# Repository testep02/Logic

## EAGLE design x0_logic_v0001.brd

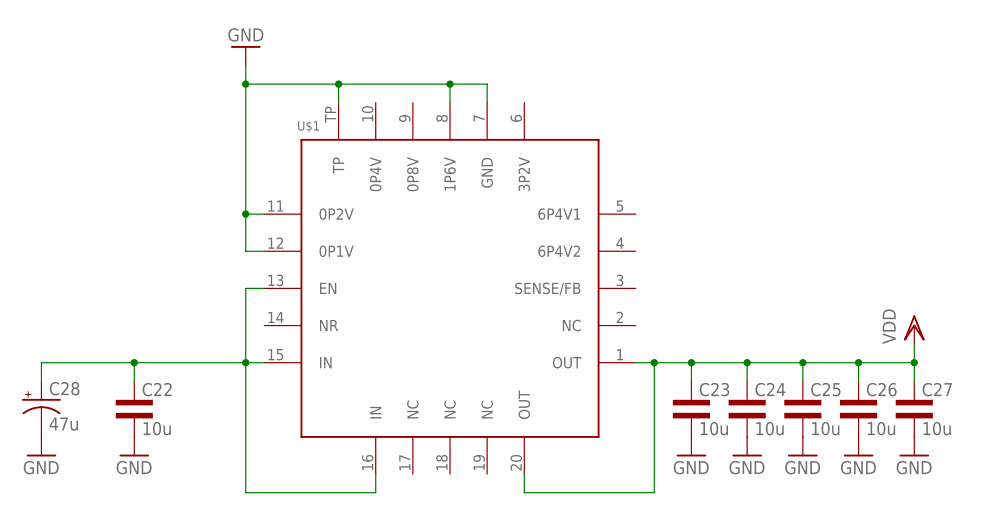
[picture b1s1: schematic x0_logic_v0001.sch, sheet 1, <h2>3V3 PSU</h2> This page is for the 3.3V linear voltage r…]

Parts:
C22, C23, C24, C25, C26, C27: 10u; 1206L3
C28: 47u; CT7343
U$1: POWER-SUPPLY_POS_V1_TI_LDO_TPS7A4700; POWER-SUPPLY_POS_V1_TI_LDO_VQFN-20

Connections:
BATT+: C22.1, C28.+, U$1.13 (EN), U$1.15 (IN), U$1.16 (IN); also elsewhere on the board
GND: C22.2, C23.2, C24.2, C25.2, C26.2, C27.2, C28.-, U$1.7 (GND), U$1.8 (1P6V), U$1.11 (0P2V), U$1.12 (0P1V), U$1.TP; also elsewhere on the board
VDD: C23.1, C24.1, C25.1, C26.1, C27.1, U$1.1 (OUT), U$1.20 (OUT); also elsewhere on the board

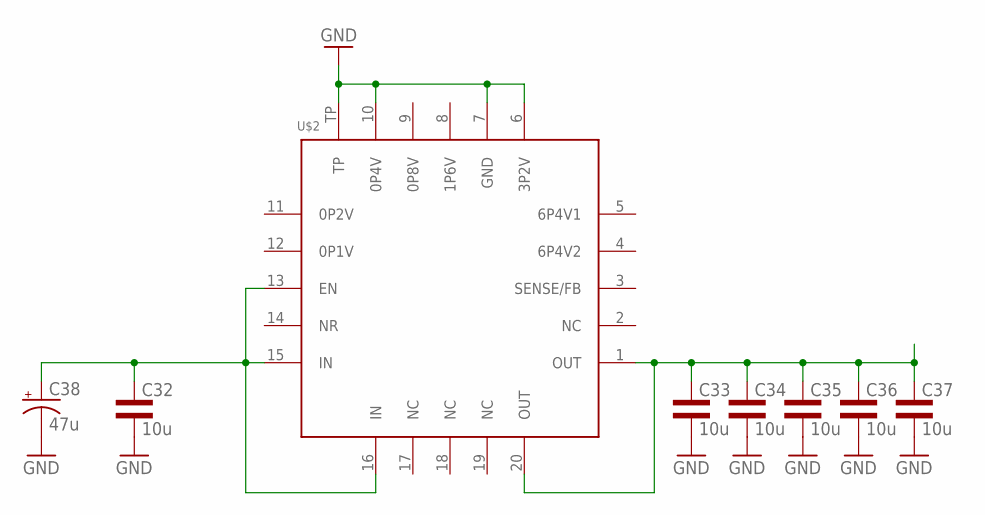
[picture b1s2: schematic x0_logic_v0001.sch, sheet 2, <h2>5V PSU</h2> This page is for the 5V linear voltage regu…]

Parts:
C32, C33, C34, C35, C36, C37: 10u; 1206L3
C38: 47u; CT7343
U$2: POWER-SUPPLY_POS_V1_TI_LDO_TPS7A4700; POWER-SUPPLY_POS_V1_TI_LDO_VQFN-20

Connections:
5V: C33.1, C34.1, C35.1, C36.1, C37.1, U$2.1 (OUT), U$2.20 (OUT); also elsewhere on the board
BATT+: C32.1, C38.+, U$2.13 (EN), U$2.15 (IN), U$2.16 (IN); also elsewhere on the board
GND: C32.2, C33.2, C34.2, C35.2, C36.2, C37.2, C38.-, U$2.6 (3P2V), U$2.7 (GND), U$2.10 (0P4V), U$2.TP; also elsewhere on the board

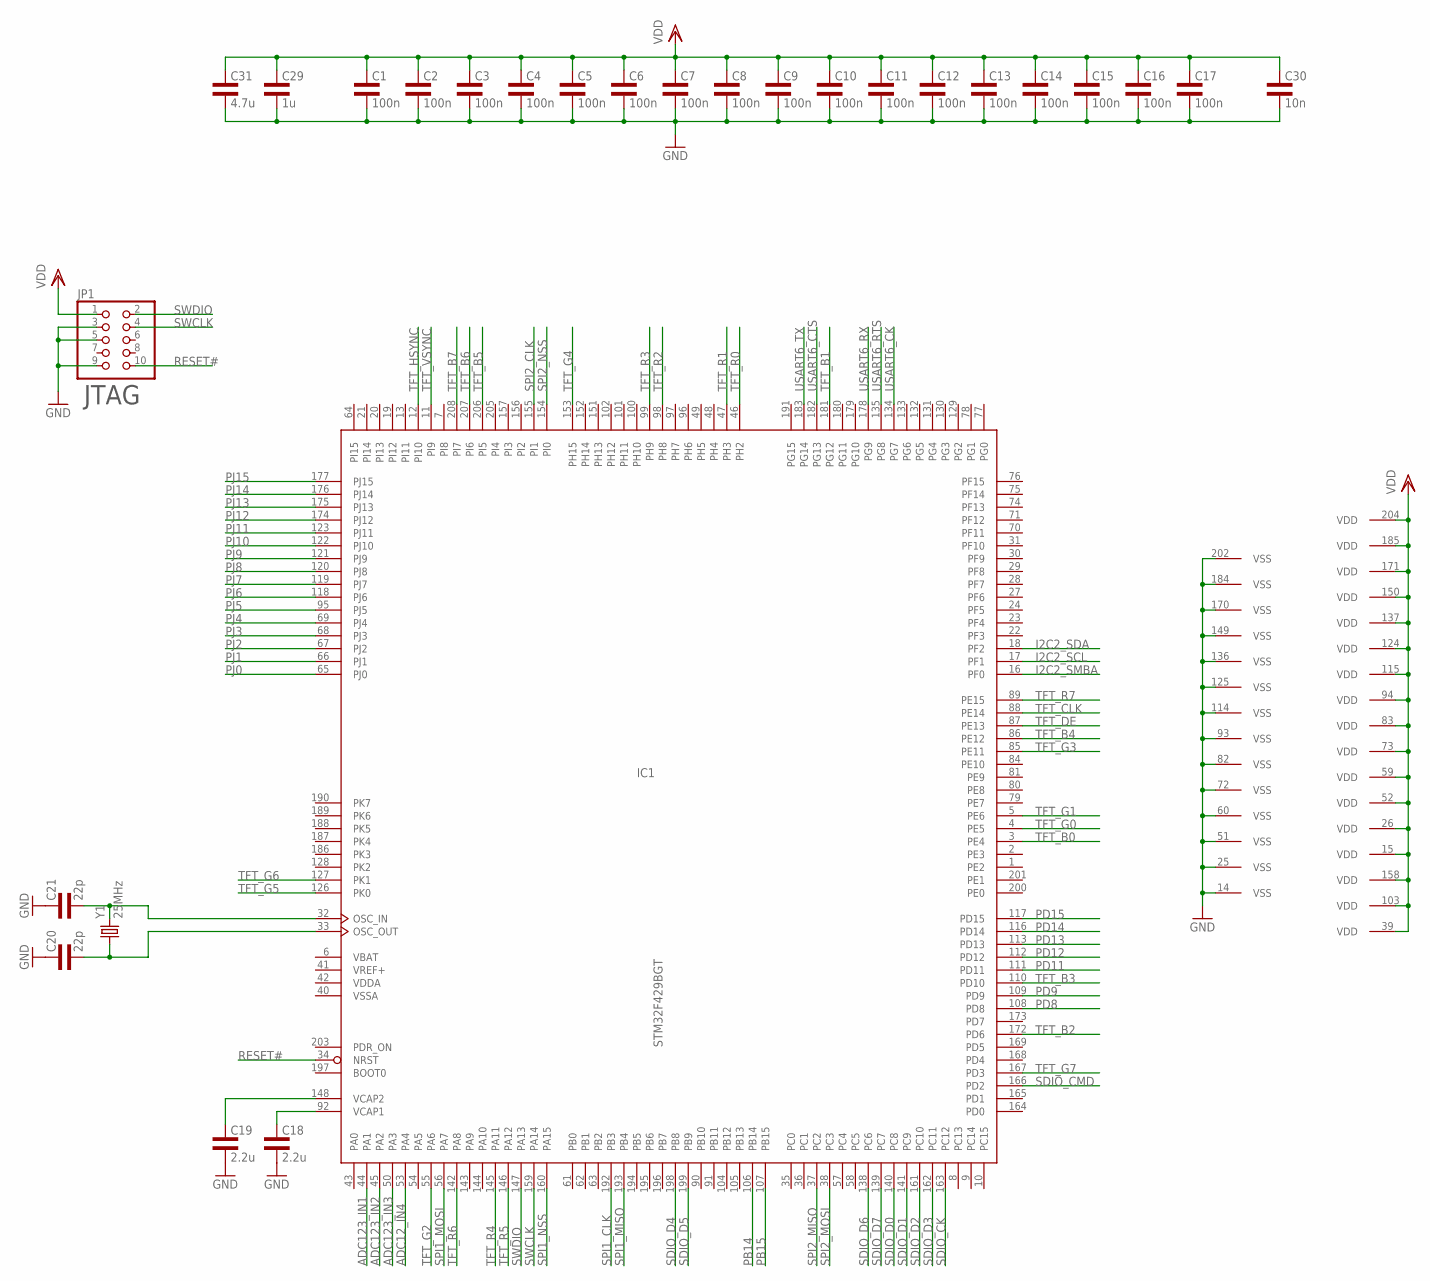
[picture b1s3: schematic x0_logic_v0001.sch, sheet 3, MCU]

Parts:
C1, C2, C3, C4, C5, C6, C7, C8, C9, C10, C11, C12, C13, C14, C15, C16, C17: 100n; 0402L3
C18, C19: 2.2u; 0603L3
C20, C21: 22p; 0402L3
C29: 1u; 0805L3
C30: 10n; 0603L3
C31: 4.7u; 0805L3
IC1: STM32F429BGT; LQFP208
JP1: PINHD-2X5; 2X05
Y1: 25MHz; HC49US

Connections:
ADC12_IN4: IC1.53 (PA4); also elsewhere on the board
ADC123_IN1: IC1.44 (PA1); also elsewhere on the board
ADC123_IN2: IC1.45 (PA2); also elsewhere on the board
ADC123_IN3: IC1.50 (PA3); also elsewhere on the board
GND: C1.P$2 (2), C2.P$2 (2), C3.P$2 (2), C4.P$2 (2), C5.P$2 (2), C6.P$2 (2), C7.P$2 (2), C8.P$2 (2), C9.P$2 (2), C10.P$2 (2), C11.P$2 (2), C12.P$2 (2), C13.P$2 (2), C14.P$2 (2), C15.P$2 (2), C16.P$2 (2), C17.P$2 (2), C18.P$2 (2), C19.P$2 (2), C20.P$1 (1), C21.P$1 (1), C29.2, C30.P$2 (2), C31.2, IC1.14 (VSS), IC1.25 (VSS), IC1.51 (VSS), IC1.60 (VSS), IC1.72 (VSS), IC1.82 (VSS), IC1.93 (VSS), IC1.114 (VSS), IC1.125 (VSS), IC1.136 (VSS), IC1.149 (VSS), IC1.170 (VSS), IC1.184 (VSS), IC1.202 (VSS), JP1.3, JP1.5, JP1.9; also elsewhere on the board
I2C2_SCL: IC1.17 (PF1); also elsewhere on the board
I2C2_SDA: IC1.18 (PF2); also elsewhere on the board
I2C2_SMBA: IC1.16 (PF0); also elsewhere on the board
unnamed: C18.P$1 (1), IC1.92 (VCAP1)
unnamed: C19.P$1 (1), IC1.148 (VCAP2)
unnamed: C20.P$2 (2), IC1.33 (OSC_OUT), Y1.1
unnamed: C21.P$2 (2), IC1.32 (OSC_IN), Y1.2
PB14: IC1.106 (PB14)
PB15: IC1.107 (PB15); also elsewhere on the board
PD8: IC1.108 (PD8)
PD9: IC1.109 (PD9)
PD11: IC1.111 (PD11)
PD12: IC1.112 (PD12)
PD13: IC1.113 (PD13)
PD14: IC1.116 (PD14)
PD15: IC1.117 (PD15)
PJ0: IC1.65 (PJ0); also elsewhere on the board
PJ1: IC1.66 (PJ1); also elsewhere on the board
PJ2: IC1.67 (PJ2); also elsewhere on the board
PJ3: IC1.68 (PJ3); also elsewhere on the board
PJ4: IC1.69 (PJ4); also elsewhere on the board
PJ5: IC1.95 (PJ5); also elsewhere on the board
PJ6: IC1.118 (PJ6); also elsewhere on the board
PJ7: IC1.119 (PJ7); also elsewhere on the board
PJ8: IC1.120 (PJ8); also elsewhere on the board
PJ9: IC1.121 (PJ9); also elsewhere on the board
PJ10: IC1.122 (PJ10); also elsewhere on the board
PJ11: IC1.123 (PJ11); also elsewhere on the board
PJ12: IC1.174 (PJ12); also elsewhere on the board
PJ13: IC1.175 (PJ13); also elsewhere on the board
PJ14: IC1.176 (PJ14); also elsewhere on the board
PJ15: IC1.177 (PJ15); also elsewhere on the board
RESET#: IC1.34 (NRST), JP1.10
SDIO_CK: IC1.163 (PC12); also elsewhere on the board
SDIO_CMD: IC1.166 (PD2); also elsewhere on the board
SDIO_D0: IC1.140 (PC8); also elsewhere on the board
SDIO_D1: IC1.141 (PC9); also elsewhere on the board
SDIO_D2: IC1.161 (PC10); also elsewhere on the board
SDIO_D3: IC1.162 (PC11); also elsewhere on the board
SDIO_D4: IC1.198 (PB8)
SDIO_D5: IC1.199 (PB9)
SDIO_D6: IC1.138 (PC6)
SDIO_D7: IC1.139 (PC7)
SPI1_CLK: IC1.192 (PB3); also elsewhere on the board
SPI1_MISO: IC1.193 (PB4); also elsewhere on the board
SPI1_MOSI: IC1.56 (PA7); also elsewhere on the board
SPI1_NSS: IC1.160 (PA15); also elsewhere on the board
SPI2_CLK: IC1.155 (PI1); also elsewhere on the board
SPI2_MISO: IC1.37 (PC2); also elsewhere on the board
SPI2_MOSI: IC1.38 (PC3); also elsewhere on the board
SPI2_NSS: IC1.154 (PI0); also elsewhere on the board
SWCLK: IC1.159 (PA14), JP1.4
SWDIO: IC1.147 (PA13), JP1.2
TFT_B0: IC1.3 (PE4); also elsewhere on the board
TFT_B1: IC1.181 (PG12); also elsewhere on the board
TFT_B2: IC1.172 (PD6); also elsewhere on the board
TFT_B3: IC1.110 (PD10); also elsewhere on the board
TFT_B4: IC1.86 (PE12); also elsewhere on the board
TFT_B5: IC1.206 (PI5); also elsewhere on the board
TFT_B6: IC1.207 (PI6); also elsewhere on the board
TFT_B7: IC1.208 (PI7); also elsewhere on the board
TFT_CLK: IC1.88 (PE14); also elsewhere on the board
TFT_DE: IC1.87 (PE13); also elsewhere on the board
TFT_G0: IC1.4 (PE5); also elsewhere on the board
TFT_G1: IC1.5 (PE6); also elsewhere on the board
TFT_G2: IC1.55 (PA6); also elsewhere on the board
TFT_G3: IC1.85 (PE11); also elsewhere on the board
TFT_G4: IC1.153 (PH15); also elsewhere on the board
TFT_G5: IC1.126 (PK0); also elsewhere on the board
TFT_G6: IC1.127 (PK1); also elsewhere on the board
TFT_G7: IC1.167 (PD3); also elsewhere on the board
TFT_HSYNC: IC1.12 (PI10); also elsewhere on the board
TFT_R0: IC1.46 (PH2); also elsewhere on the board
TFT_R1: IC1.47 (PH3); also elsewhere on the board
TFT_R2: IC1.98 (PH8); also elsewhere on the board
TFT_R3: IC1.99 (PH9); also elsewhere on the board
TFT_R4: IC1.145 (PA11); also elsewhere on the board
TFT_R5: IC1.146 (PA12); also elsewhere on the board
TFT_R6: IC1.142 (PA8); also elsewhere on the board
TFT_R7: IC1.89 (PE15); also elsewhere on the board
TFT_VSYNC: IC1.11 (PI9); also elsewhere on the board
USART6_CK: IC1.134 (PG7)
USART6_CTS: IC1.182 (PG13)
USART6_RTS: IC1.135 (PG8)
USART6_RX: IC1.178 (PG9)
USART6_TX: IC1.183 (PG14)
VBAT: IC1.6 (VBAT)
VDD: C1.P$1 (1), C2.P$1 (1), C3.P$1 (1), C4.P$1 (1), C5.P$1 (1), C6.P$1 (1), C7.P$1 (1), C8.P$1 (1), C9.P$1 (1), C10.P$1 (1), C11.P$1 (1), C12.P$1 (1), C13.P$1 (1), C14.P$1 (1), C15.P$1 (1), C16.P$1 (1), C17.P$1 (1), C29.1, C30.P$1 (1), C31.1, IC1.15 (VDD), IC1.26 (VDD), IC1.39 (VDD), IC1.52 (VDD), IC1.59 (VDD), IC1.73 (VDD), IC1.83 (VDD), IC1.94 (VDD), IC1.103 (VDD), IC1.115 (VDD), IC1.124 (VDD), IC1.137 (VDD), IC1.150 (VDD), IC1.158 (VDD), IC1.171 (VDD), IC1.185 (VDD), IC1.204 (VDD), JP1.1; also elsewhere on the board
VDDA: IC1.42 (VDDA)
VREF+: IC1.41 (VREF+)
VSSA: IC1.40 (VSSA)

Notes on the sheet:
JTAG

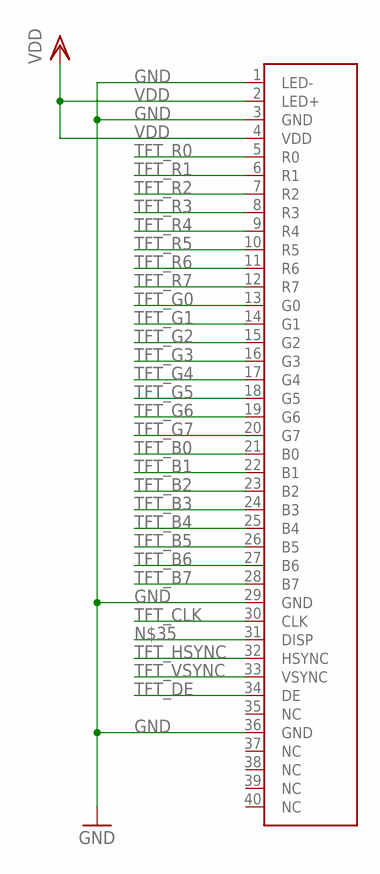
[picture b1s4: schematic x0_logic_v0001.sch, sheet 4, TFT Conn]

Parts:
CON1: NH-4.3; FPC-40

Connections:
GND: CON1.1 (LED-), CON1.3 (GND), CON1.29 (GND), CON1.36 (GND); also elsewhere on the board
TFT_B0: CON1.21 (B0); also elsewhere on the board
TFT_B1: CON1.22 (B1); also elsewhere on the board
TFT_B2: CON1.23 (B2); also elsewhere on the board
TFT_B3: CON1.24 (B3); also elsewhere on the board
TFT_B4: CON1.25 (B4); also elsewhere on the board
TFT_B5: CON1.26 (B5); also elsewhere on the board
TFT_B6: CON1.27 (B6); also elsewhere on the board
TFT_B7: CON1.28 (B7); also elsewhere on the board
TFT_CLK: CON1.30 (CLK); also elsewhere on the board
TFT_DE: CON1.34 (DE); also elsewhere on the board
TFT_G0: CON1.13 (G0); also elsewhere on the board
TFT_G1: CON1.14 (G1); also elsewhere on the board
TFT_G2: CON1.15 (G2); also elsewhere on the board
TFT_G3: CON1.16 (G3); also elsewhere on the board
TFT_G4: CON1.17 (G4); also elsewhere on the board
TFT_G5: CON1.18 (G5); also elsewhere on the board
TFT_G6: CON1.19 (G6); also elsewhere on the board
TFT_G7: CON1.20 (G7); also elsewhere on the board
TFT_HSYNC: CON1.32 (HSYNC); also elsewhere on the board
TFT_R0: CON1.5 (R0); also elsewhere on the board
TFT_R1: CON1.6 (R1); also elsewhere on the board
TFT_R2: CON1.7 (R2); also elsewhere on the board
TFT_R3: CON1.8 (R3); also elsewhere on the board
TFT_R4: CON1.9 (R4); also elsewhere on the board
TFT_R5: CON1.10 (R5); also elsewhere on the board
TFT_R6: CON1.11 (R6); also elsewhere on the board
TFT_R7: CON1.12 (R7); also elsewhere on the board
TFT_VSYNC: CON1.33 (VSYNC); also elsewhere on the board
VDD: CON1.2 (LED+), CON1.4 (VDD); also elsewhere on the board

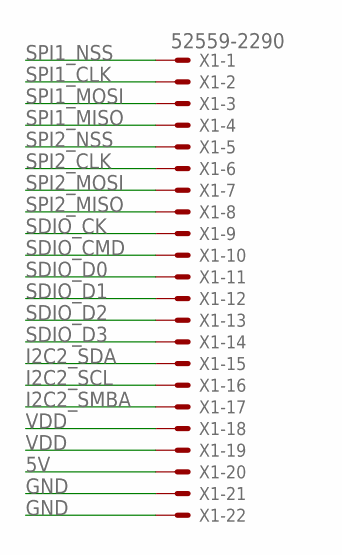
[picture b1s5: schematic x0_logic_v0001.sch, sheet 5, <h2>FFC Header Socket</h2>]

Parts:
X1: 52559-2290

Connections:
5V: X1.20; also elsewhere on the board
GND: X1.21, X1.22; also elsewhere on the board
I2C2_SCL: X1.16; also elsewhere on the board
I2C2_SDA: X1.15; also elsewhere on the board
I2C2_SMBA: X1.17; also elsewhere on the board
SDIO_CK: X1.9; also elsewhere on the board
SDIO_CMD: X1.10; also elsewhere on the board
SDIO_D0: X1.11; also elsewhere on the board
SDIO_D1: X1.12; also elsewhere on the board
SDIO_D2: X1.13; also elsewhere on the board
SDIO_D3: X1.14; also elsewhere on the board
SPI1_CLK: X1.2; also elsewhere on the board
SPI1_MISO: X1.4; also elsewhere on the board
SPI1_MOSI: X1.3; also elsewhere on the board
SPI1_NSS: X1.1; also elsewhere on the board
SPI2_CLK: X1.6; also elsewhere on the board
SPI2_MISO: X1.8; also elsewhere on the board
SPI2_MOSI: X1.7; also elsewhere on the board
SPI2_NSS: X1.5; also elsewhere on the board
VDD: X1.18, X1.19; also elsewhere on the board

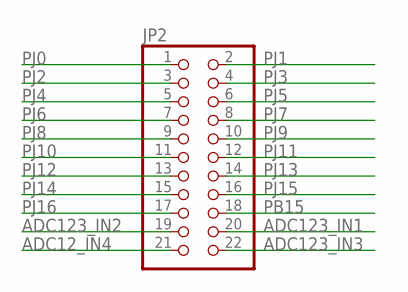
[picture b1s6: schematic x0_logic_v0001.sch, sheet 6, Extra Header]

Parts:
JP2: PINHD-2X11; 2X11

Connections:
ADC12_IN4: JP2.21; also elsewhere on the board
ADC123_IN1: JP2.20; also elsewhere on the board
ADC123_IN2: JP2.19; also elsewhere on the board
ADC123_IN3: JP2.22; also elsewhere on the board
PB15: JP2.18; also elsewhere on the board
PJ0: JP2.1; also elsewhere on the board
PJ1: JP2.2; also elsewhere on the board
PJ2: JP2.3; also elsewhere on the board
PJ3: JP2.4; also elsewhere on the board
PJ4: JP2.5; also elsewhere on the board
PJ5: JP2.6; also elsewhere on the board
PJ6: JP2.7; also elsewhere on the board
PJ7: JP2.8; also elsewhere on the board
PJ8: JP2.9; also elsewhere on the board
PJ9: JP2.10; also elsewhere on the board
PJ10: JP2.11; also elsewhere on the board
PJ11: JP2.12; also elsewhere on the board
PJ12: JP2.13; also elsewhere on the board
PJ13: JP2.14; also elsewhere on the board
PJ14: JP2.15; also elsewhere on the board
PJ15: JP2.16; also elsewhere on the board
PJ16: JP2.17

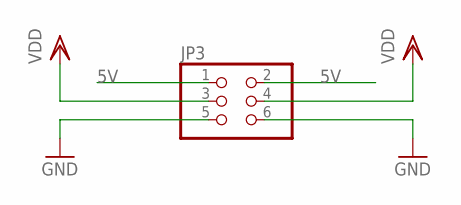
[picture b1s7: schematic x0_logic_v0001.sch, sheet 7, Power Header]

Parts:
JP3: PINHD-2X3; 2X03

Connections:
5V: JP3.1, JP3.2; also elsewhere on the board
GND: JP3.5, JP3.6; also elsewhere on the board
VDD: JP3.3, JP3.4; also elsewhere on the board

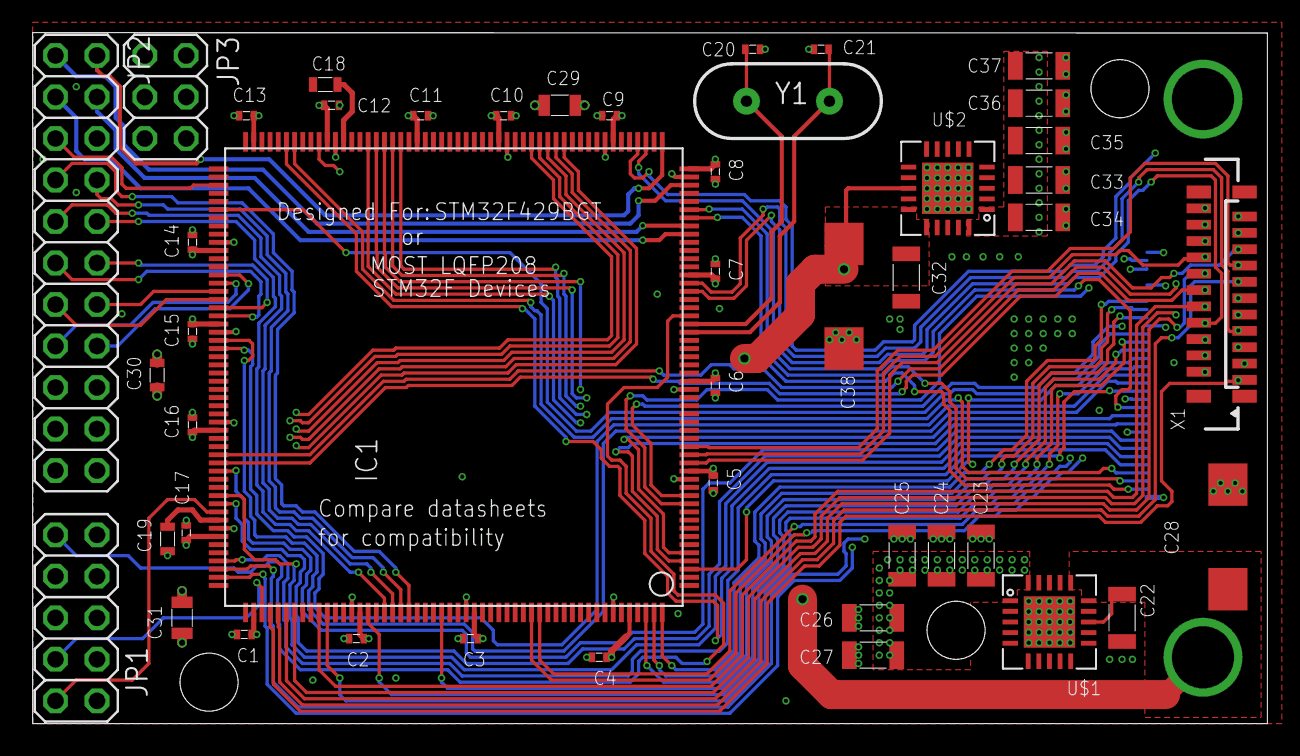
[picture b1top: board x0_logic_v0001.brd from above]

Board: 4 copper layers, 75.6 x 42.3 mm, 47 parts (1 on the bottom side), 77 nets.

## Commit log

2017-03-01 Initial commit of Vape - X0 - Controller board

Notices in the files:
parts and their libraries:
SparkFun-FreqCtrl: Licensing: CC v3.0 Share-Alike You are welcome to use this library for commercial purposes.
